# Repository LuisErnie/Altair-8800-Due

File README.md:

# Altair-8800-Due
Arduino **Altair 8800** Simulator hardware platform based on the specification of the project by David Hansel at [Hackster](https://www.hackster.io/david-hansel/arduino-altair-8800-simulator-3594a6#schematics)

Hardware platform is designed for the **Due** variant of the project in **Autodesk Eagle 9.5.2** as a complete enclosure with serial port output and front control pannel in 3:10 scale. The Project is fully working with address and function switches operating as on the original design.

Design: Luis Ernesto Fernández R, December 2019.

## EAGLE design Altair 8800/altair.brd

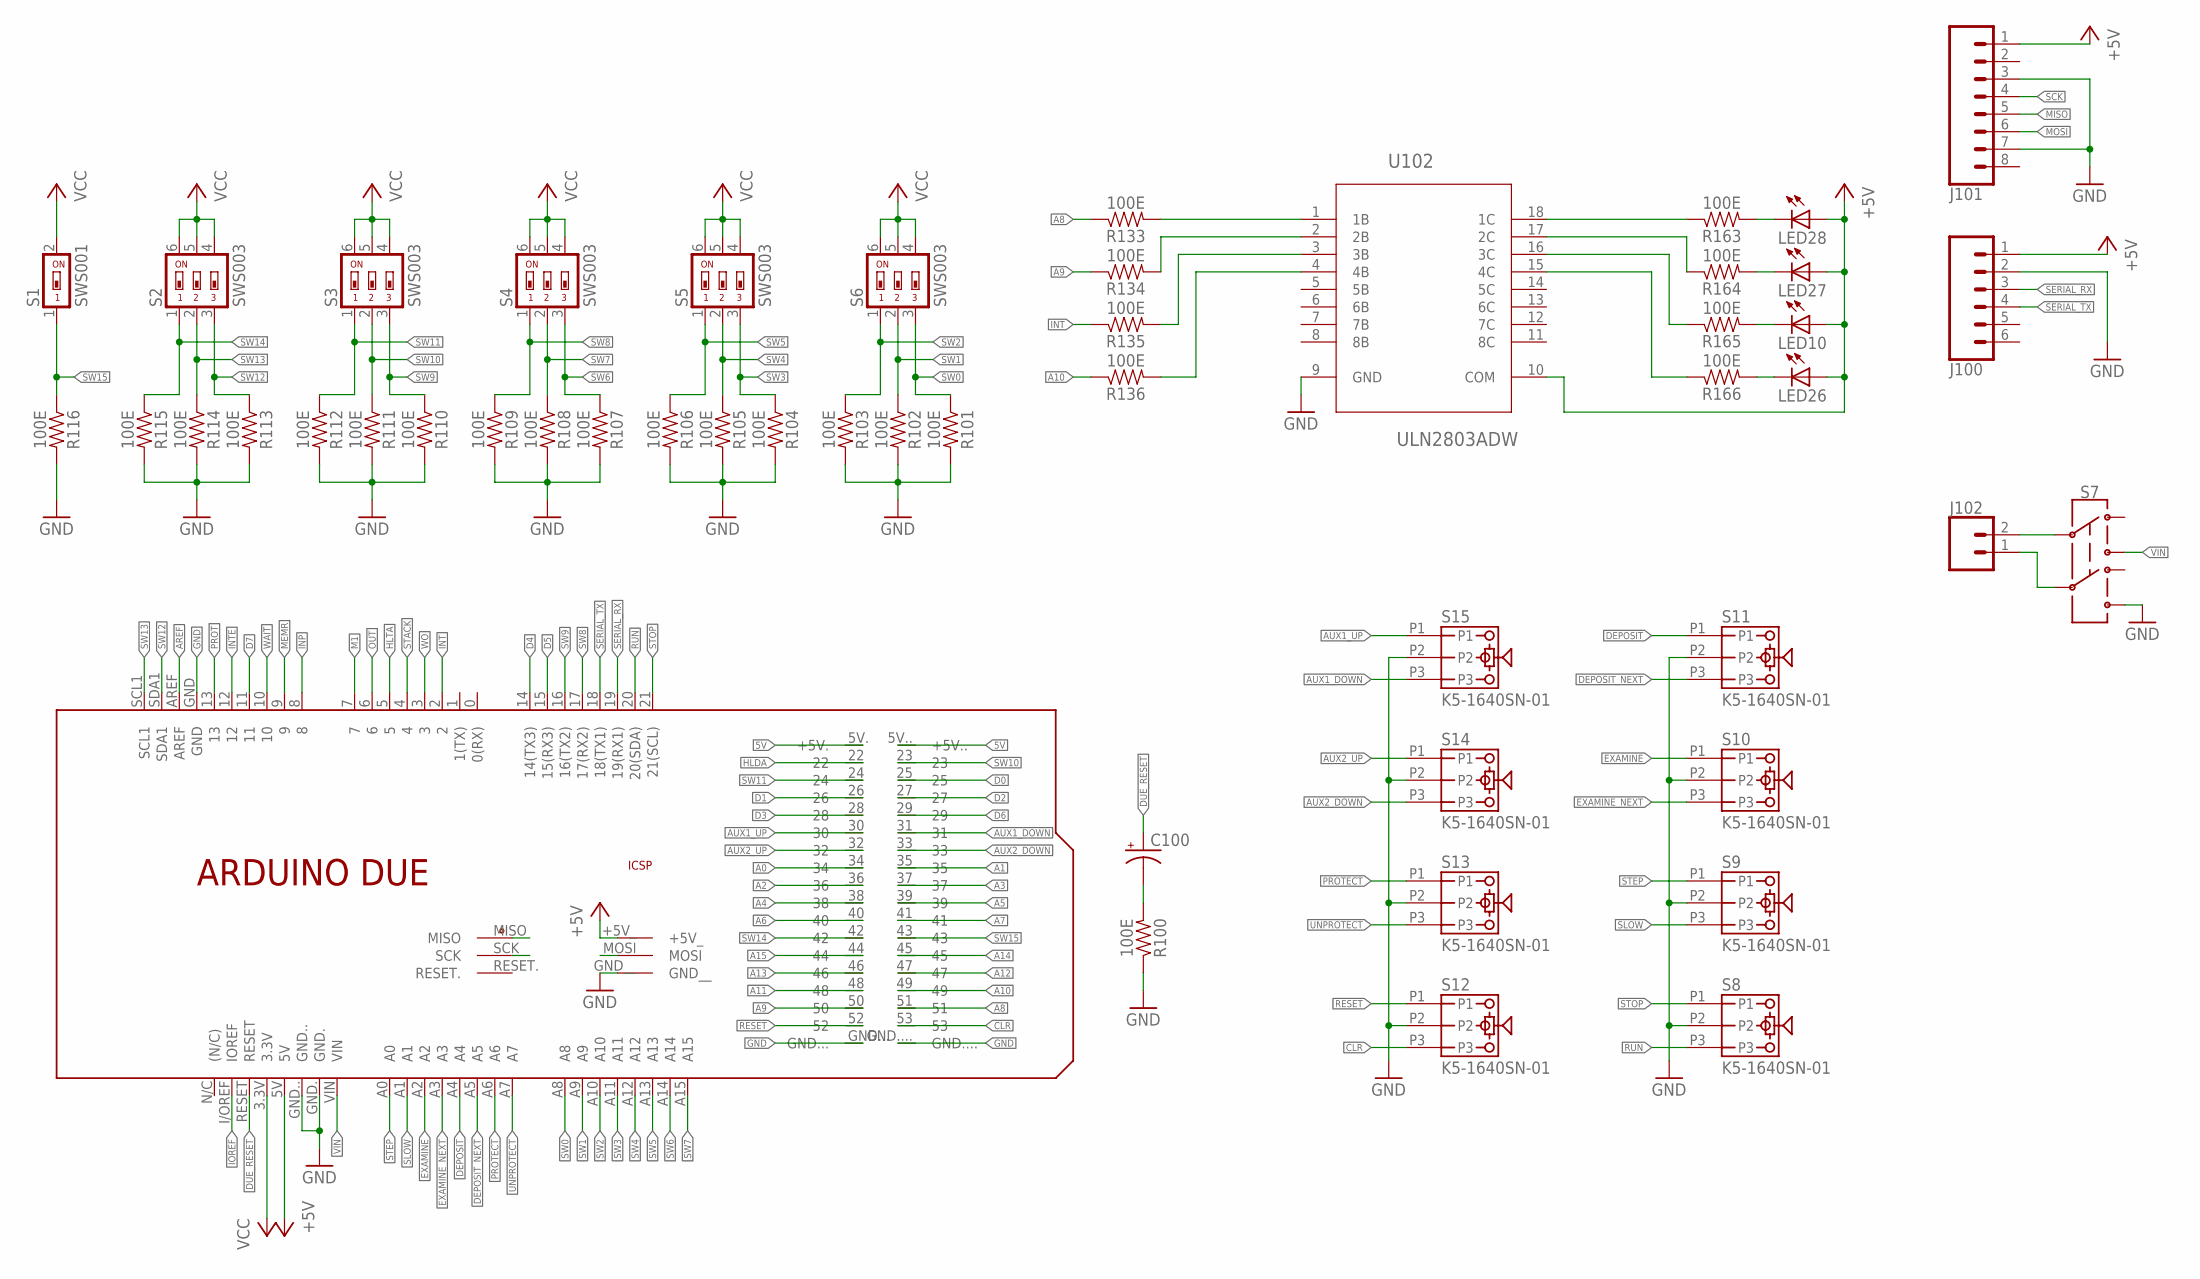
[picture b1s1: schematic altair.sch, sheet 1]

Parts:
C100: CPOL-USD; PANASONIC_D
J100: CONN_06LOCK; 1X06_LOCK
J101: CONN_08LOCK; 1X08_LOCK
J102: CONN_02POLAR_LOCK; MOLEX-1X2_LOCK
LED10, LED26, LED27, LED28: LEDCHIP-LED0805; CHIP-LED0805
PCB1: ARDUINO_DUEARDUINO_DUE; ARDUINO_MEGA2560
R100, R101, R102, R103, R104, R105, R106, R107, R108, R109, R110, R111, R112, R113, R114, R115, R116, R133, R134, R135, R136, R163, R164, R165, R166: 100E; 0805
S1: SWS001; SMS-001
S2, S3, S4, S5, S6: SWS003; SMS-003
S7: SWITCH-DPDT-SMD-AYZ0202; SWITCH_DPDT_SMD_AYZ0202
S8, S9, S10, S11, S12, S13, S14, S15: K5-1640SN-01
U102: ULN2803ADW; SOIC127P1030X265-18N

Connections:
5V: PCB1.5V. (+5V.), PCB1.5V.. (+5V..)
+5V: J100.1, J101.1, LED10.A, LED26.A, LED27.A, LED28.A, PCB1.5V, PCB1.+5V_, U102.10 (COM); also elsewhere on the board
A0: PCB1.34; also elsewhere on the board
A1: PCB1.35; also elsewhere on the board
A2: PCB1.36; also elsewhere on the board
A3: PCB1.37; also elsewhere on the board
A4: PCB1.38; also elsewhere on the board
A5: PCB1.39; also elsewhere on the board
A6: PCB1.40; also elsewhere on the board
A7: PCB1.41; also elsewhere on the board
A8: PCB1.51, R133.1
A9: PCB1.50, R134.1
A10: PCB1.49, R136.1
A11: PCB1.48; also elsewhere on the board
A12: PCB1.47; also elsewhere on the board
A13: PCB1.46; also elsewhere on the board
A14: PCB1.45; also elsewhere on the board
A15: PCB1.44; also elsewhere on the board
AREF: PCB1.AREF
AUX1_DOWN: PCB1.31, S15.P3
AUX1_UP: PCB1.30, S15.P1
AUX2_DOWN: PCB1.33, S14.P3
AUX2_UP: PCB1.32, S14.P1
CLR: PCB1.53, S12.P3
D0: PCB1.25; also elsewhere on the board
D1: PCB1.26; also elsewhere on the board
D2: PCB1.27; also elsewhere on the board
D3: PCB1.28; also elsewhere on the board
D4: PCB1.14 (14(TX3)); also elsewhere on the board
D5: PCB1.15 (15(RX3)); also elsewhere on the board
D6: PCB1.29; also elsewhere on the board
D7: PCB1.11; also elsewhere on the board
DEPOSIT: PCB1.A4, S11.P1
DEPOSIT_NEXT: PCB1.A5, S11.P3
DUE_RESET: C100.+, PCB1.RESET
EXAMINE: PCB1.A2, S10.P1
EXAMINE_NEXT: PCB1.A3, S10.P3
GND: J100.2, J101.3, J101.7, PCB1.GND, PCB1.GND., PCB1.GND.., PCB1.GND..., PCB1.GND...., PCB1.GND__, R100.1, R101.2, R102.2, R103.2, R104.2, R105.2, R106.2, R107.2, R108.2, R109.2, R110.2, R111.2, R112.2, R113.2, R114.2, R115.2, R116.2, S7.6, S8.P2, S9.P2, S10.P2, S11.P2, S12.P2, S13.P2, S14.P2, S15.P2, U102.9 (GND); also elsewhere on the board
HLDA: PCB1.22; also elsewhere on the board
HLTA: PCB1.5; also elsewhere on the board
INP: PCB1.8; also elsewhere on the board
INT: PCB1.2, R135.1
INTE: PCB1.12; also elsewhere on the board
IOREF: PCB1.I/OREF (IOREF)
M1: PCB1.7; also elsewhere on the board
MEMR: PCB1.9; also elsewhere on the board
MISO: J101.5, PCB1.MISO
MOSI: J101.6, PCB1.MOSI
unnamed: LED28.C, R163.2
unnamed: LED27.C, R164.2
unnamed: LED10.C, R165.2
unnamed: LED26.C, R166.2
unnamed: R163.1, U102.18 (1C)
unnamed: R164.1, U102.17 (2C)
unnamed: R165.1, U102.16 (3C)
unnamed: R166.1, U102.15 (4C)
unnamed: C100.-, R100.2
unnamed: R133.2, U102.1 (1B)
unnamed: R134.2, U102.2 (2B)
unnamed: R135.2, U102.3 (3B)
unnamed: R136.2, U102.4 (4B)
unnamed: J102.2, S7.2
unnamed: J102.1, S7.5
OUT: PCB1.6; also elsewhere on the board
PROT: PCB1.13; also elsewhere on the board
PROTECT: PCB1.A6, S13.P1
RESET: PCB1.52, S12.P1
RUN: PCB1.20 (20(SDA)), S8.P3
SCK: J101.4, PCB1.SCK
SERIAL_RX: J100.3, PCB1.19 (19(RX1))
SERIAL_TX: J100.4, PCB1.18 (18(TX1))
SLOW: PCB1.A1, S9.P3
STACK: PCB1.4; also elsewhere on the board
STEP: PCB1.A0, S9.P1
STOP: PCB1.21 (21(SCL)), S8.P1
SW0: PCB1.A8, R101.1, S6.3
SW1: PCB1.A9, R102.1, S6.2
SW2: PCB1.A10, R103.1, S6.1
SW3: PCB1.A11, R104.1, S5.3
SW4: PCB1.A12, R105.1, S5.2
SW5: PCB1.A13, R106.1, S5.1
SW6: PCB1.A14, R107.1, S4.3
SW7: PCB1.A15, R108.1, S4.2
SW8: PCB1.17 (17(RX2)), R109.1, S4.1
SW9: PCB1.16 (16(TX2)), R110.1, S3.3
SW10: PCB1.23, R111.1, S3.2
SW11: PCB1.24, R112.1, S3.1
SW12: PCB1.SDA1, R113.1, S2.3
SW13: PCB1.SCL1, R114.1, S2.2
SW14: PCB1.42, R115.1, S2.1
SW15: PCB1.43, R116.1, S1.1
UNPROTECT: PCB1.A7, S13.P3
VCC: PCB1.3.3V, S1.2, S2.4, S2.5, S2.6, S3.4, S3.5, S3.6, S4.4, S4.5, S4.6, S5.4, S5.5, S5.6, S6.4, S6.5, S6.6
VIN: PCB1.VIN, S7.3
WAIT: PCB1.10; also elsewhere on the board
WO: PCB1.3; also elsewhere on the board

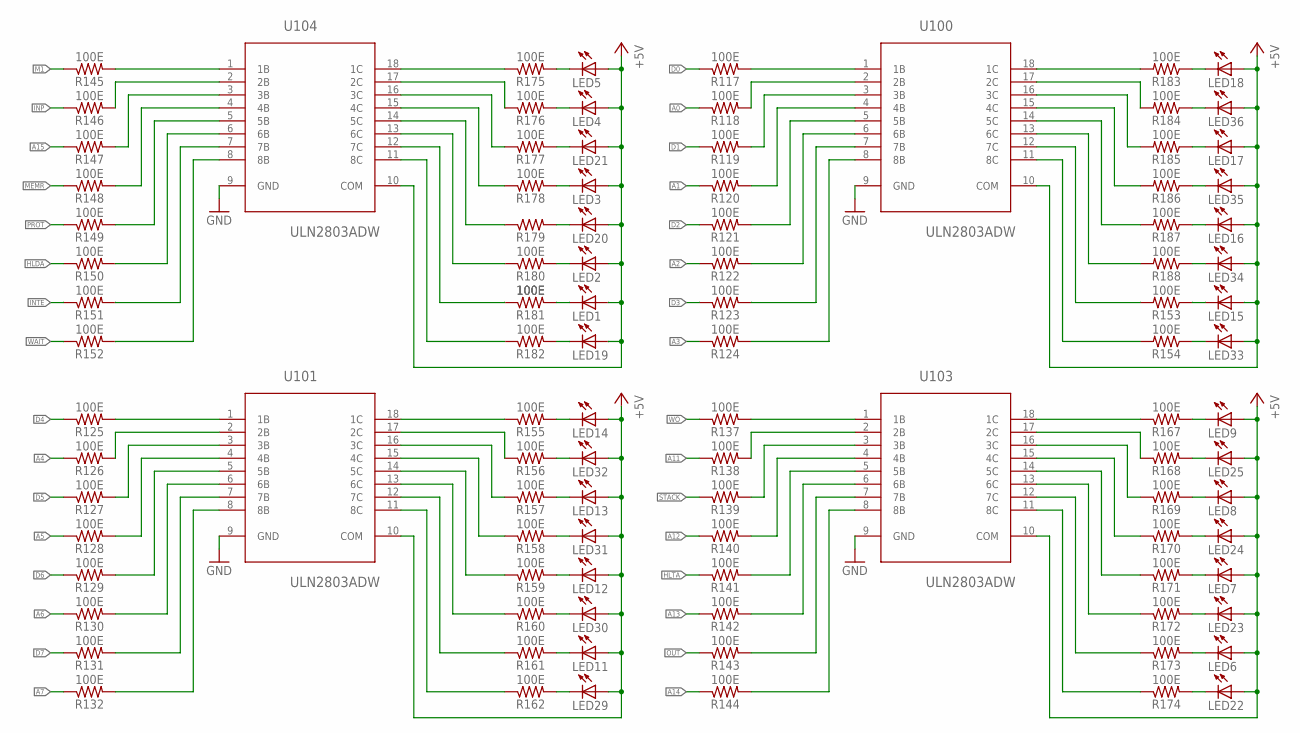
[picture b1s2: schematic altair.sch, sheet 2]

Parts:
LED1, LED2, LED3, LED4, LED5, LED6, LED7, LED8, LED9, LED11, LED12, LED13, LED14, LED15, LED16, LED17, LED18, LED19, LED20, LED21, LED22, LED23, LED24, LED25, LED29, LED30, LED31, LED32, LED33, LED34, LED35, LED36: LEDCHIP-LED0805; CHIP-LED0805
R117, R118, R119, R120, R121, R122, R123, R124, R125, R126, R127, R128, R129, R130, R131, R132, R137, R138, R139, R140, R141, R142, R143, R144, R145, R146, R147, R148, R149, R150, R151, R152, R153, R154, R155, R156, R157, R158, R159, R160, R161, R162, R167, R168, R169, R170, R171, R172, R173, R174, R175, R176, R177, R178, R179, R180, R181, R182, R183, R184, R185, R186, R187, R188: 100E; 0805
U100, U101, U103, U104: ULN2803ADW; SOIC127P1030X265-18N

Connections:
+5V: LED1.A, LED2.A, LED3.A, LED4.A, LED5.A, LED6.A, LED7.A, LED8.A, LED9.A, LED11.A, LED12.A, LED13.A, LED14.A, LED15.A, LED16.A, LED17.A, LED18.A, LED19.A, LED20.A, LED21.A, LED22.A, LED23.A, LED24.A, LED25.A, LED29.A, LED30.A, LED31.A, LED32.A, LED33.A, LED34.A, LED35.A, LED36.A, U100.10 (COM), U101.10 (COM), U103.10 (COM), U104.10 (COM); also elsewhere on the board
A0: R118.1; also elsewhere on the board
A1: R120.1; also elsewhere on the board
A2: R122.1; also elsewhere on the board
A3: R124.1; also elsewhere on the board
A4: R126.1; also elsewhere on the board
A5: R128.1; also elsewhere on the board
A6: R130.1; also elsewhere on the board
A7: R132.1; also elsewhere on the board
A11: R138.1; also elsewhere on the board
A12: R140.1; also elsewhere on the board
A13: R142.1; also elsewhere on the board
A14: R144.1; also elsewhere on the board
A15: R147.1; also elsewhere on the board
D0: R117.1; also elsewhere on the board
D1: R119.1; also elsewhere on the board
D2: R121.1; also elsewhere on the board
D3: R123.1; also elsewhere on the board
D4: R125.1; also elsewhere on the board
D5: R127.1; also elsewhere on the board
D6: R129.1; also elsewhere on the board
D7: R131.1; also elsewhere on the board
GND: U100.9 (GND), U101.9 (GND), U103.9 (GND), U104.9 (GND); also elsewhere on the board
HLDA: R150.1; also elsewhere on the board
HLTA: R141.1; also elsewhere on the board
INP: R146.1; also elsewhere on the board
INTE: R151.1; also elsewhere on the board
M1: R145.1; also elsewhere on the board
MEMR: R148.1; also elsewhere on the board
unnamed: R183.2, U100.18 (1C)
unnamed: R184.2, U100.17 (2C)
unnamed: R185.2, U100.16 (3C)
unnamed: R186.2, U100.15 (4C)
unnamed: R187.2, U100.14 (5C)
unnamed: R188.2, U100.13 (6C)
unnamed: R153.2, U100.12 (7C)
unnamed: LED5.C, R175.2
unnamed: LED4.C, R176.2
unnamed: R154.2, U100.11 (8C)
unnamed: LED18.C, R183.1
unnamed: LED36.C, R184.1
unnamed: LED17.C, R185.1
unnamed: LED21.C, R177.2
unnamed: LED3.C, R178.2
unnamed: LED20.C, R179.2
unnamed: LED2.C, R180.2
unnamed: LED1.C, R181.2
unnamed: LED19.C, R182.2
unnamed: R181.1, U104.12 (7C)
unnamed: R176.1, U104.17 (2C)
unnamed: R177.1, U104.16 (3C)
unnamed: R178.1, U104.15 (4C)
unnamed: R179.1, U104.14 (5C)
unnamed: R180.1, U104.13 (6C)
unnamed: R182.1, U104.11 (8C)
unnamed: R175.1, U104.18 (1C)
unnamed: R145.2, U104.1 (1B)
unnamed: R146.2, U104.2 (2B)
unnamed: R147.2, U104.3 (3B)
unnamed: R148.2, U104.4 (4B)
unnamed: R149.2, U104.5 (5B)
unnamed: R150.2, U104.6 (6B)
unnamed: R151.2, U104.7 (7B)
unnamed: R152.2, U104.8 (8B)
unnamed: LED35.C, R186.1
unnamed: LED16.C, R187.1
unnamed: LED34.C, R188.1
unnamed: LED15.C, R153.1
unnamed: LED33.C, R154.1
unnamed: LED9.C, R167.2
unnamed: R173.1, U103.12 (7C)
unnamed: R174.1, U103.11 (8C)
unnamed: LED25.C, R168.2
unnamed: LED8.C, R169.2
unnamed: LED24.C, R170.2
unnamed: LED7.C, R171.2
unnamed: LED23.C, R172.2
unnamed: LED6.C, R173.2
unnamed: LED22.C, R174.2
unnamed: R167.1, U103.18 (1C)
unnamed: R117.2, U100.1 (1B)
unnamed: R118.2, U100.2 (2B)
unnamed: R119.2, U100.3 (3B)
unnamed: R120.2, U100.4 (4B)
unnamed: R121.2, U100.5 (5B)
unnamed: R122.2, U100.6 (6B)
unnamed: R123.2, U100.7 (7B)
unnamed: R124.2, U100.8 (8B)
unnamed: R161.1, U101.12 (7C)
unnamed: R162.1, U101.11 (8C)
unnamed: LED14.C, R155.2
unnamed: LED32.C, R156.2
unnamed: LED13.C, R157.2
unnamed: LED31.C, R158.2
unnamed: LED12.C, R159.2
unnamed: LED30.C, R160.2
unnamed: LED11.C, R161.2
unnamed: R156.1, U101.17 (2C)
unnamed: R157.1, U101.16 (3C)
unnamed: R158.1, U101.15 (4C)
unnamed: R159.1, U101.14 (5C)
unnamed: R160.1, U101.13 (6C)
unnamed: LED29.C, R162.2
unnamed: R155.1, U101.18 (1C)
unnamed: R125.2, U101.1 (1B)
unnamed: R126.2, U101.2 (2B)
unnamed: R127.2, U101.3 (3B)
unnamed: R128.2, U101.4 (4B)
unnamed: R129.2, U101.5 (5B)
unnamed: R130.2, U101.6 (6B)
unnamed: R131.2, U101.7 (7B)
unnamed: R132.2, U101.8 (8B)
unnamed: R168.1, U103.17 (2C)
unnamed: R169.1, U103.16 (3C)
unnamed: R170.1, U103.15 (4C)
unnamed: R171.1, U103.14 (5C)
unnamed: R172.1, U103.13 (6C)
unnamed: R137.2, U103.1 (1B)
unnamed: R138.2, U103.2 (2B)
unnamed: R139.2, U103.3 (3B)
unnamed: R140.2, U103.4 (4B)
unnamed: R141.2, U103.5 (5B)
unnamed: R142.2, U103.6 (6B)
unnamed: R143.2, U103.7 (7B)
unnamed: R144.2, U103.8 (8B)
OUT: R143.1; also elsewhere on the board
PROT: R149.1; also elsewhere on the board
STACK: R139.1; also elsewhere on the board
WAIT: R152.1; also elsewhere on the board
WO: R137.1; also elsewhere on the board

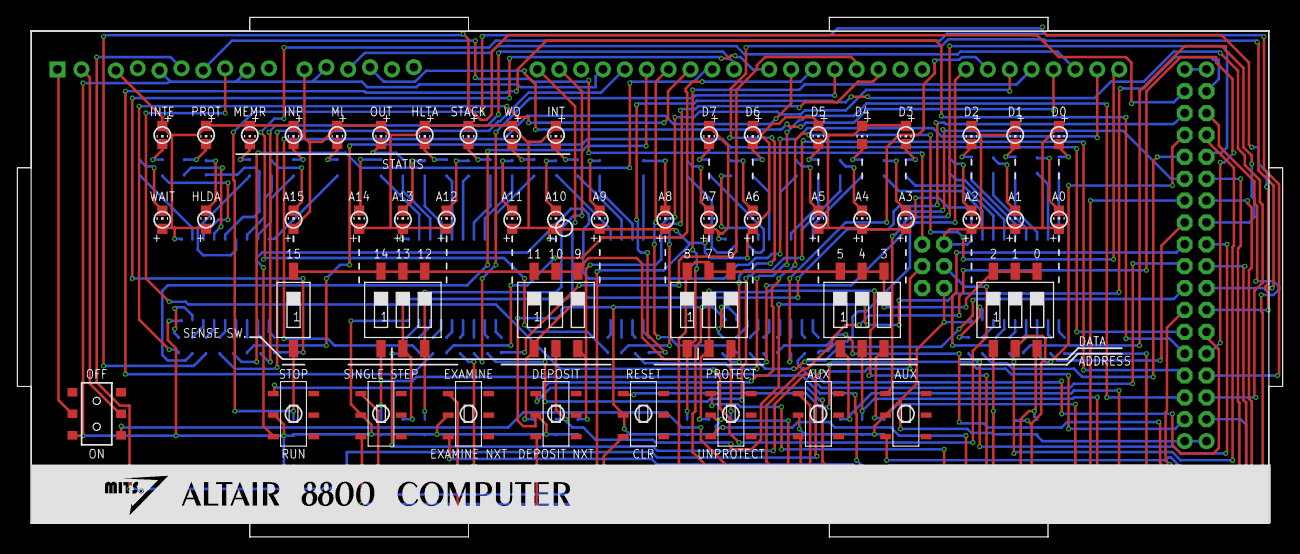
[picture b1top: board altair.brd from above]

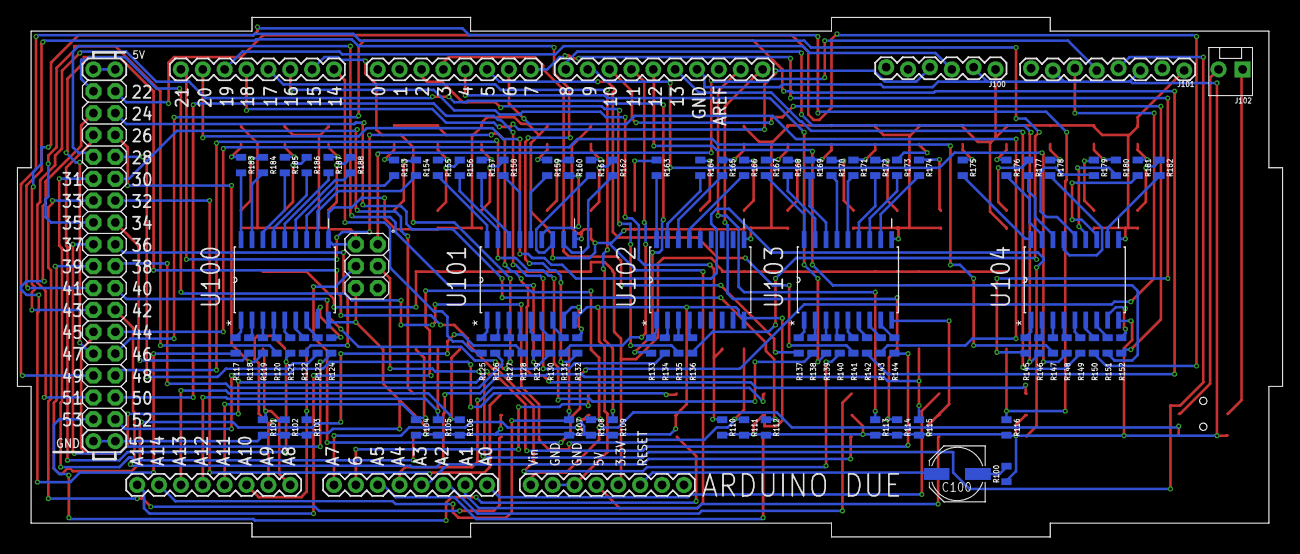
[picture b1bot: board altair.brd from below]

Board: 2 copper layers, 147.0 x 60.4 mm, 150 parts (98 on the bottom side), 190 nets.

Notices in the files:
parts and their libraries:
SparkFun-Aesthetics: Licensing: Creative Commons ShareAlike 4.0 International - https://creativecommons.org/licenses/by-sa/4.0
